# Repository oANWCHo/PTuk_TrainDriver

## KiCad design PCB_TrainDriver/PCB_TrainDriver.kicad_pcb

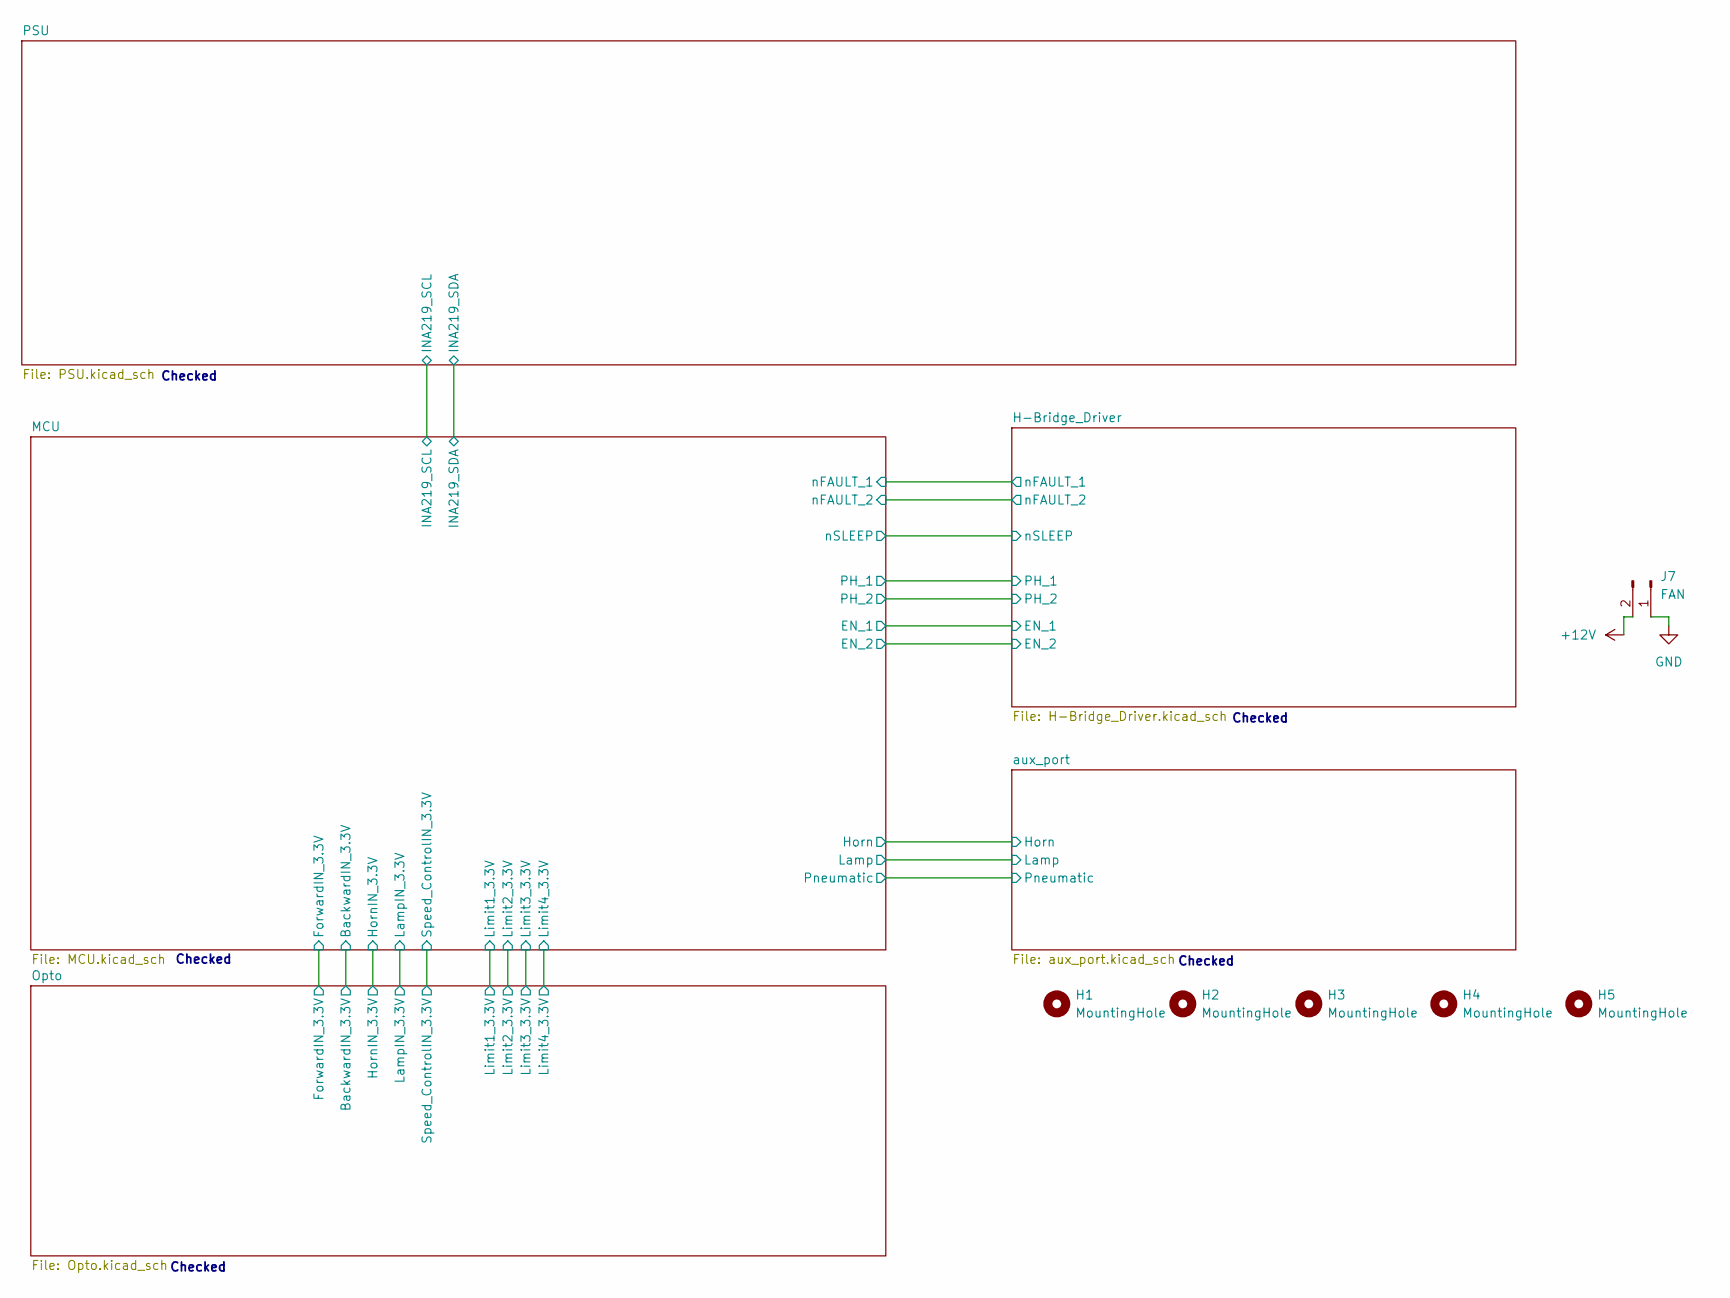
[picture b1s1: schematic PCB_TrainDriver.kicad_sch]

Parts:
H1, H2, H3, H4, H5: MountingHole; MountingHole_5.3mm_M5_DIN965_Pad
J7: FAN; JST_XA_B02B-XASK-1_1x02_P2.50mm_Vertical; JLCPCB Part # C265283

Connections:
+12V: J7.2; also elsewhere on the board
GND: J7.1; also elsewhere on the board

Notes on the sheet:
Checked

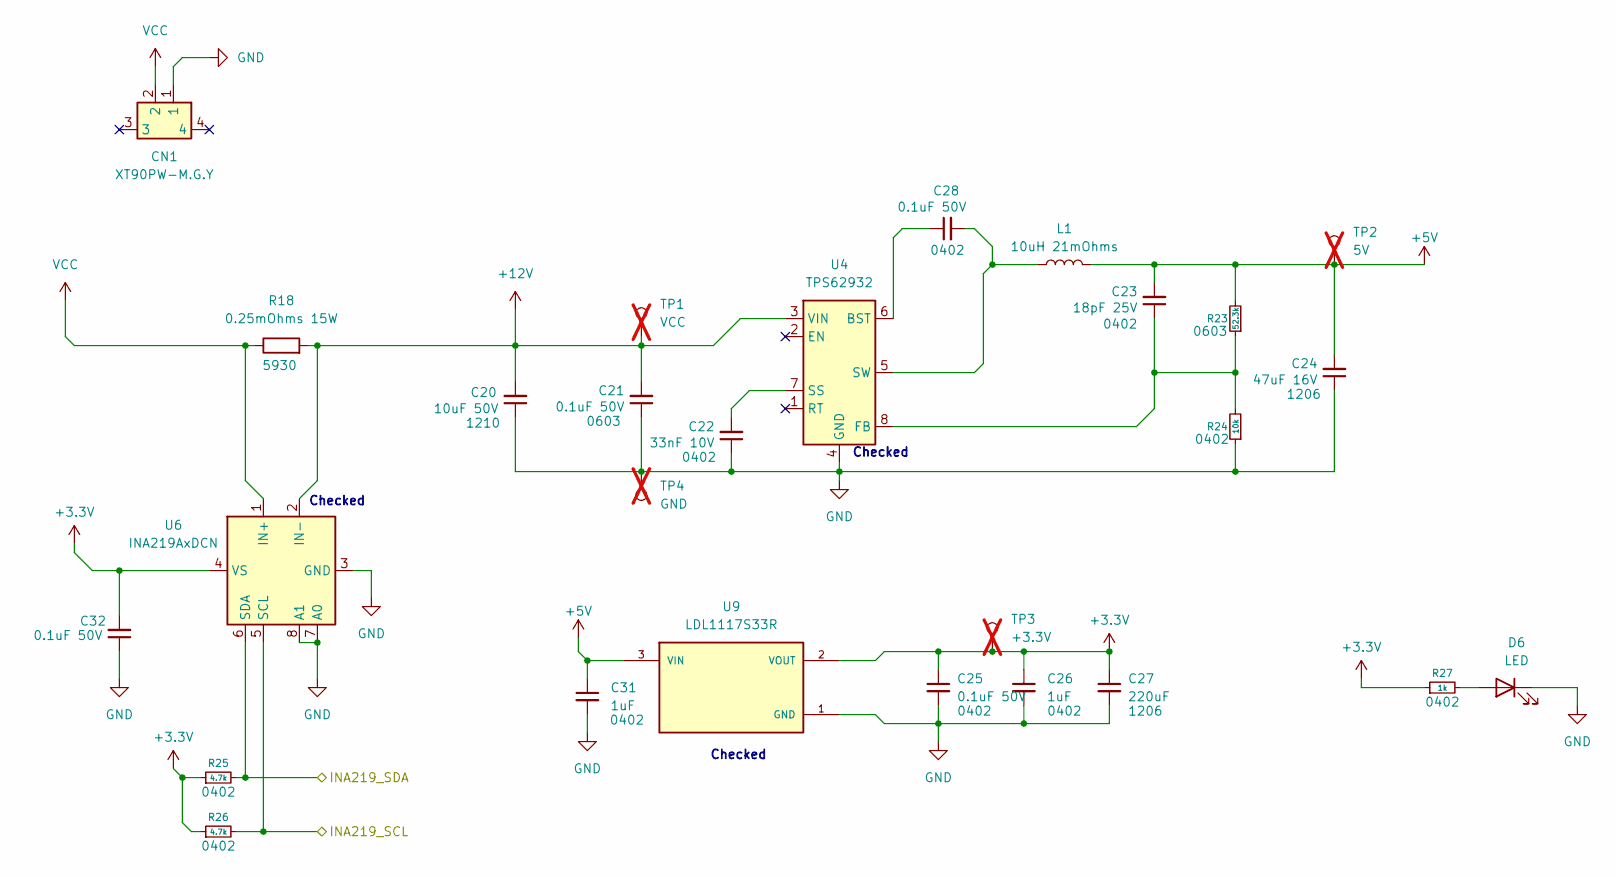
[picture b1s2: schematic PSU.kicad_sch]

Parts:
C20: 10uF 50V; C_1206_3216Metric; JLCPCB Part # C13585
C21: 0.1uF 50V; C_0603_1608Metric; JLCPCB Part # C14663
C22: 33nF 10V; C_0402_1005Metric; JLCPCB Part # C527022
C23: 18pF 25V; C_0402_1005Metric; JLCPCB Part # C526984
C24: 47uF 16V; C_1206_3216Metric; JLCPCB Part # C7472975
C25, C28, C32: 0.1uF 50V; C_0402_1005Metric; JLCPCB Part # C307331
C26, C31: 1uF; C_0402_1005Metric; JLCPCB Part # C52923
C27: 220uF; C_1206_3216Metric; JLCPCB Part # C412252
CN1: XT90PW-M.G.Y; CONN-TH_XT90PW-M.G.Y; Manufacturer Part XT90PW-M.G.Y; LCSC Part Name AMASS(艾迈斯)PCB焊板式卧式航模连接器 锂电池大电流插头 30A二芯P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
D6: LED; LED_0603_1608Metric; JLCPCB Part # C2286
L1: 10uH 21mOhms; L_12x12mm_H4.5mm; JLCPCB Part # C9904
R18: 0.25mOhms 15W; R5930; JLCPCB Part # C495779
R23: 52.3k; R_0603_1608Metric; JLCPCB Part # C23198
R24: 10k; R_0402_1005Metric; JLCPCB Part # C60490
R25, R26: 4.7k; R_0402_1005Metric; JLCPCB Part # C25900
R27: 1k; R_0402_1005Metric; JLCPCB Part # C11702
TP1: VCC; Pin_D0.7mm_L6.5mm_W1.8mm_FlatFork; not fitted
TP2: 5V; Pin_D0.7mm_L6.5mm_W1.8mm_FlatFork; not fitted
TP3: +3.3V; Pin_D0.7mm_L6.5mm_W1.8mm_FlatFork; not fitted
TP4: GND; Pin_D0.7mm_L6.5mm_W1.8mm_FlatFork; not fitted
U4: TPS62932; SOT-583-8; JLCPCB Part # C3032935
U6: INA219AxDCN; SOT-23-8; JLCPCB Part # C87469
U9: LDL1117S33R; SOT-223-3_TabPin2; PARTREV 7; JLCPCB Part # C18906017

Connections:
+3.3V: C25.1, C26.1, C27.1, C32.2, R25.1, R26.1, R27.1, TP3.1 (1_1), U6.4 (VS), U9.2 (VOUT), U9.4 (VOUT__1); also elsewhere on the board
+5V: C23.2, C24.2, C31.1, L1.2, R23.2, TP2.1 (1_1), U9.3 (VIN)
+12V: C20.2, C21.2, R18.2, TP1.1 (1_1), U4.3 (VIN), U6.2 (IN-); also elsewhere on the board
/MCU/INA219_SCL: R26.2, U6.5 (SCL); also elsewhere on the board
/MCU/INA219_SDA: R25.2, U6.6 (SDA); also elsewhere on the board
GND: C20.1, C21.1, C22.1, C24.1, C25.2, C26.2, C27.2, C31.2, C32.1, CN1.1, D6.1 (K), R24.1, TP4.1 (1_1), U4.4 (GND), U6.3 (GND), U6.7 (A0), U6.8 (A1), U9.1 (GND); also elsewhere on the board
unnamed: D6.2 (A), R27.2
unnamed: C28.1, U4.6 (BST)
unnamed: C23.1, R23.1, R24.2, U4.8 (FB)
unnamed: C22.2, U4.7 (SS)
unnamed: C28.2, L1.1, U4.5 (SW)
VCC: CN1.2, R18.1, U6.1 (IN+)

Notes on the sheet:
Checked

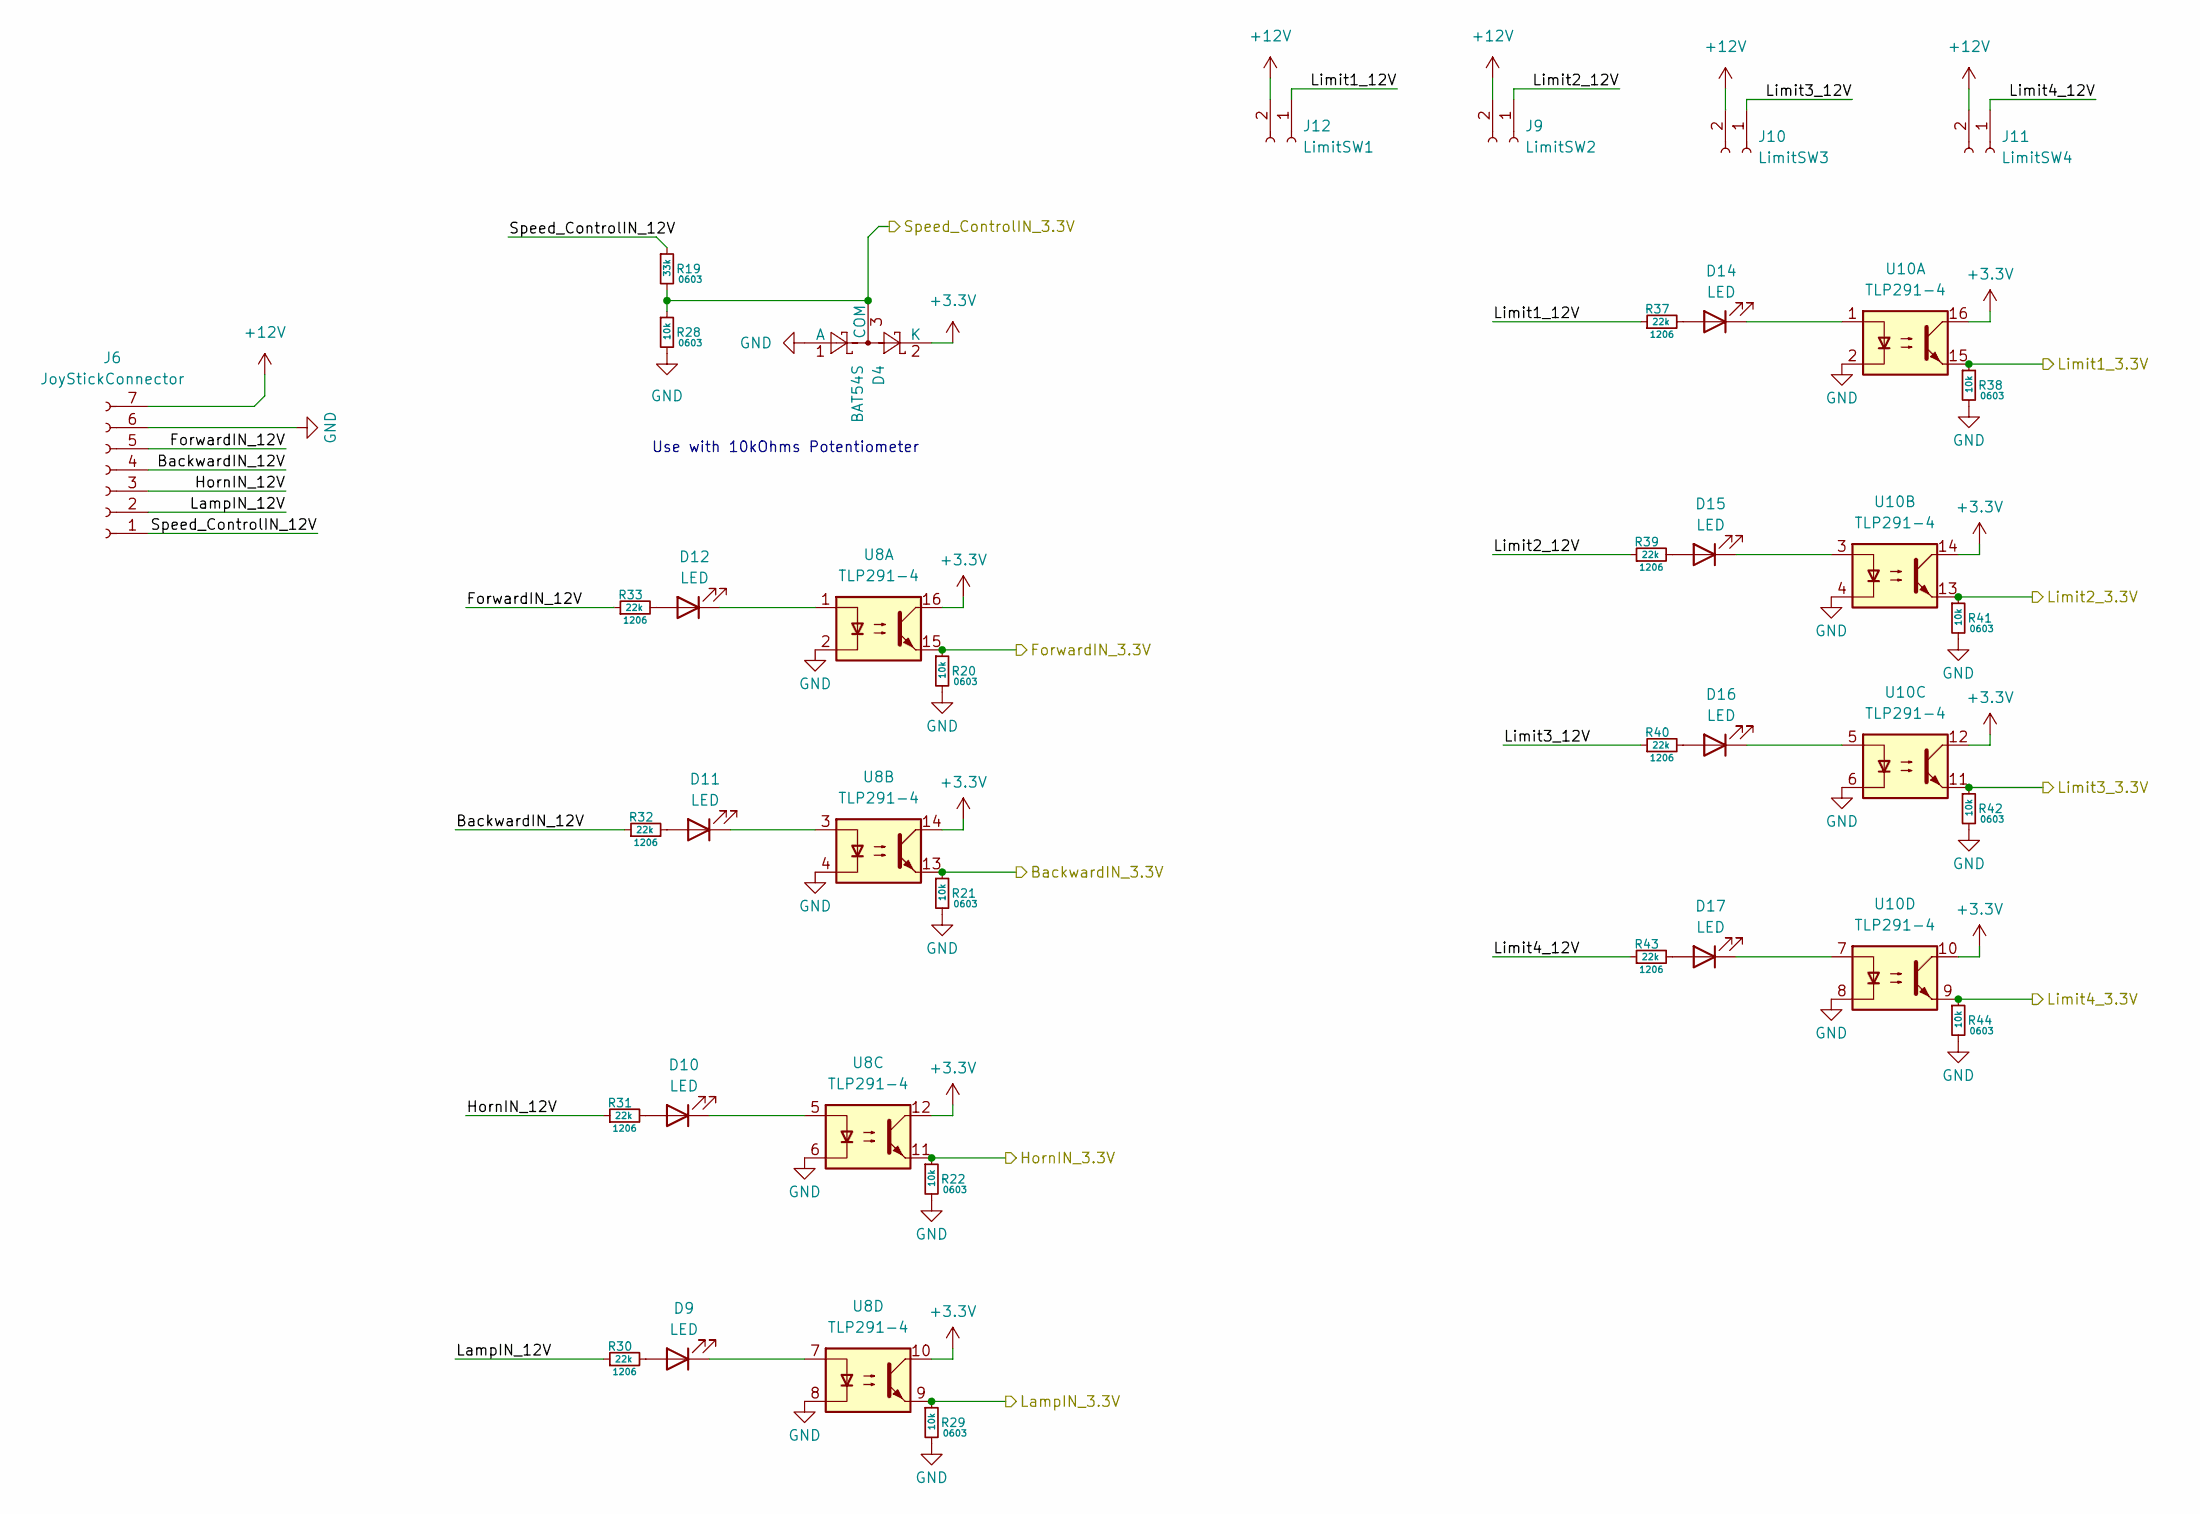
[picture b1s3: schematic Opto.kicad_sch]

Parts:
D4: BAT54S; SOT-23; JLCPCB Part # C19726
D9, D10, D11, D12, D14, D15, D16, D17: LED; LED_0603_1608Metric; JLCPCB Part # C2287
J6: JoyStickConnector; JST_XH_B7B-XH-A_1x07_P2.50mm_Vertical; JLCPCB Part # C144398
J9: LimitSW2; JST_XH_B2B-XH-A_1x02_P2.50mm_Vertical; JLCPCB Part # C265283
J10: LimitSW3; JST_XH_B2B-XH-A_1x02_P2.50mm_Vertical; JLCPCB Part # C265283
J11: LimitSW4; JST_XH_B2B-XH-A_1x02_P2.50mm_Vertical; JLCPCB Part # C265283
J12: LimitSW1; JST_XH_B2B-XH-A_1x02_P2.50mm_Vertical; JLCPCB Part # C265283
R19: 33k; R_0603_1608Metric; JLCPCB Part # C4216
R20, R21, R22, R28, R29, R38, R41, R42, R44: 10k; R_0603_1608Metric; JLCPCB Part # C25804
R30, R31, R32, R33, R37, R39, R40, R43: 22k; R_1206_3216Metric; JLCPCB Part # C25654
U8, U10: TLP291-4; SOIC-16_4.55x10.3mm_P1.27mm; JLCPCB Part # C60900

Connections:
+3.3V: D4.2 (K), U8.10, U8.12, U8.14, U8.16, U10.10, U10.12, U10.14, U10.16; also elsewhere on the board
+12V: J6.7, J9.2, J10.2, J11.2, J12.2; also elsewhere on the board
/MCU/BackwardIN_3.3V: R21.1, U8.13; also elsewhere on the board
/MCU/ForwardIN_3.3V: R20.1, U8.15; also elsewhere on the board
/MCU/HornIN_3.3V: R22.1, U8.11; also elsewhere on the board
/MCU/LampIN_3.3V: R29.1, U8.9; also elsewhere on the board
/MCU/Limit1_3.3V: R38.1, U10.15; also elsewhere on the board
/MCU/Limit2_3.3V: R41.1, U10.13; also elsewhere on the board
/MCU/Limit3_3.3V: R42.1, U10.11; also elsewhere on the board
/MCU/Limit4_3.3V: R44.1, U10.9; also elsewhere on the board
/MCU/Speed_ControlIN_3.3V: D4.3 (COM), R19.2, R28.1; also elsewhere on the board
/Opto/BackwardIN_12V: J6.4, R32.1
/Opto/ForwardIN_12V: J6.5, R33.1
/Opto/HornIN_12V: J6.3, R31.1
/Opto/LampIN_12V: J6.2, R30.1
/Opto/Limit1_12V: J12.1, R37.1
/Opto/Limit2_12V: J9.1, R39.1
/Opto/Limit3_12V: J10.1, R40.1
/Opto/Limit4_12V: J11.1, R43.1
/Opto/Speed_ControlIN_12V: J6.1, R19.1
GND: D4.1 (A), J6.6, R20.2, R21.2, R22.2, R28.2, R29.2, R38.2, R41.2, R42.2, R44.2, U8.2, U8.4, U8.6, U8.8, U10.2, U10.4, U10.6, U10.8; also elsewhere on the board
unnamed: D9.2 (A), R30.2
unnamed: D9.1 (K), U8.7
unnamed: D10.2 (A), R31.2
unnamed: D10.1 (K), U8.5
unnamed: D11.2 (A), R32.2
unnamed: D11.1 (K), U8.3
unnamed: D12.2 (A), R33.2
unnamed: D12.1 (K), U8.1
unnamed: D14.2 (A), R37.2
unnamed: D14.1 (K), U10.1
unnamed: D15.2 (A), R39.2
unnamed: D15.1 (K), U10.3
unnamed: D16.2 (A), R40.2
unnamed: D16.1 (K), U10.5
unnamed: D17.2 (A), R43.2
unnamed: D17.1 (K), U10.7

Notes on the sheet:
Use with 10kOhms Potentiometer

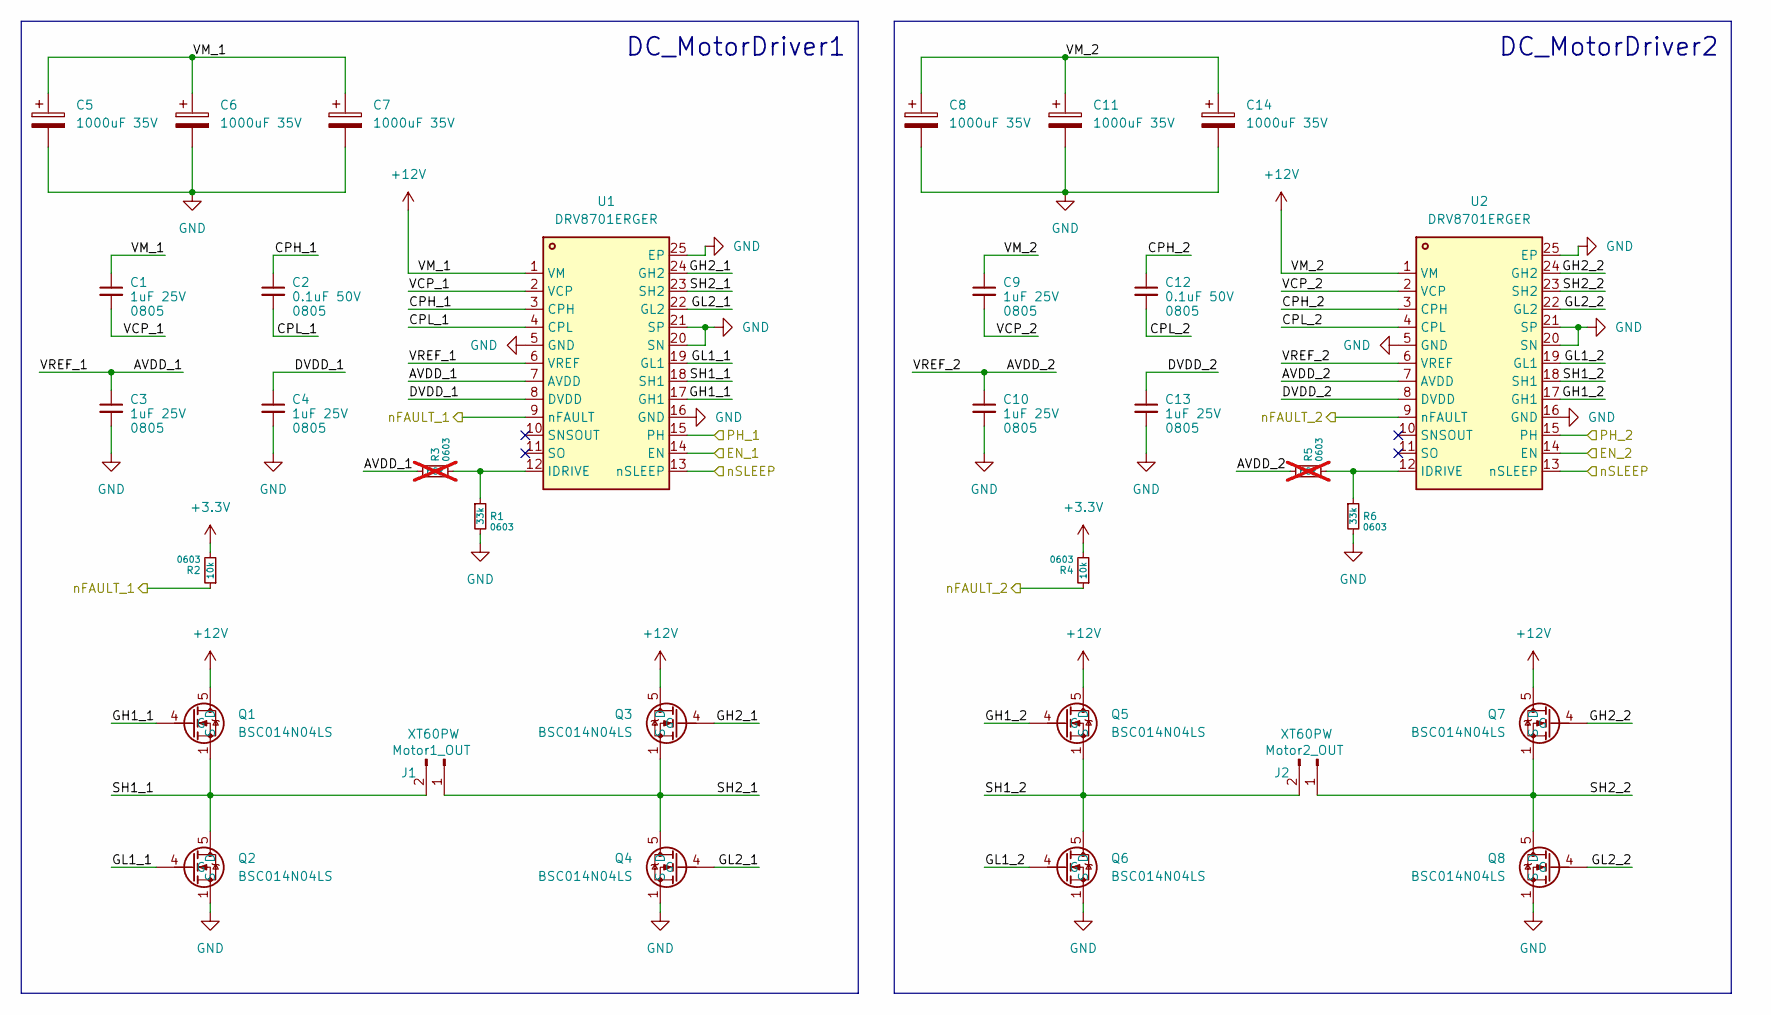
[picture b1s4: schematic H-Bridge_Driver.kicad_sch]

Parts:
C1, C3, C4, C9, C10, C13: 1uF 25V; C_0805_2012Metric; JLCPCB Part # C5137482
C2, C12: 0.1uF 50V; C_0805_2012Metric; JLCPCB Part # C49678
C5, C6, C7, C8, C11, C14: 1000uF 35V; CP_Elec_10x10; JLCPCB Part # C46550395
J1: Motor1_OUT; AMASS_XT60PW-M_1x02_P7.20mm_Horizontal; JLCPCB Part # C98732
J2: Motor2_OUT; AMASS_XT60PW-M_1x02_P7.20mm_Horizontal; JLCPCB Part # C98732
Q1, Q2, Q3, Q4, Q5, Q6, Q7, Q8: BSC014N04LS; Infineon_PG-TDSON-8_6.15x5.15mm; JLCPCB Part # C2760081
R1, R6: 33k; R_0603_1608Metric; JLCPCB Part # C4216
R2, R4: 10k; R_0603_1608Metric; JLCPCB Part # C25804
R3, R5: 68k; R_0603_1608Metric; JLCPCB Part # C23231; not fitted
U1, U2: DRV8701ERGER; VQFN-24-1EP_4x4mm_P0.5mm_EP2.45x2.45mm; Manufacturer Part DRV8701ERGER; JLCPCB Part # C90964

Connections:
+3.3V: R2.2, R4.2; also elsewhere on the board
+12V: C1.1, C5.1, C6.1, C7.1, C8.1, C9.1, C11.1, C14.1, Q1.5 (D), Q3.5 (D), Q5.5 (D), Q7.5 (D), U1.1 (VM), U2.1 (VM); also elsewhere on the board
/H-Bridge_Driver/AVDD_1: C3.1, R3.1, U1.6 (VREF), U1.7 (AVDD)
/H-Bridge_Driver/AVDD_2: C10.1, R5.1, U2.6 (VREF), U2.7 (AVDD)
/H-Bridge_Driver/CPH_1: C2.1, U1.3 (CPH)
/H-Bridge_Driver/CPH_2: C12.1, U2.3 (CPH)
/H-Bridge_Driver/CPL_1: C2.2, U1.4 (CPL)
/H-Bridge_Driver/CPL_2: C12.2, U2.4 (CPL)
/H-Bridge_Driver/DVDD_1: C4.1, U1.8 (DVDD)
/H-Bridge_Driver/DVDD_2: C13.1, U2.8 (DVDD)
/H-Bridge_Driver/EN_1: U1.14 (EN); also elsewhere on the board
/H-Bridge_Driver/EN_2: U2.14 (EN); also elsewhere on the board
/H-Bridge_Driver/GH1_1: Q1.4 (G), U1.17 (GH1)
/H-Bridge_Driver/GH1_2: Q5.4 (G), U2.17 (GH1)
/H-Bridge_Driver/GH2_1: Q3.4 (G), U1.24 (GH2)
/H-Bridge_Driver/GH2_2: Q7.4 (G), U2.24 (GH2)
/H-Bridge_Driver/GL1_1: Q2.4 (G), U1.19 (GL1)
/H-Bridge_Driver/GL1_2: Q6.4 (G), U2.19 (GL1)
/H-Bridge_Driver/GL2_1: Q4.4 (G), U1.22 (GL2)
/H-Bridge_Driver/GL2_2: Q8.4 (G), U2.22 (GL2)
/H-Bridge_Driver/PH_1: U1.15 (PH); also elsewhere on the board
/H-Bridge_Driver/PH_2: U2.15 (PH); also elsewhere on the board
/H-Bridge_Driver/SH1_1: J1.2, Q1.1 (S), Q1.2 (S), Q1.3 (S), Q2.5 (D), U1.18 (SH1)
/H-Bridge_Driver/SH1_2: J2.2, Q5.1 (S), Q5.2 (S), Q5.3 (S), Q6.5 (D), U2.18 (SH1)
/H-Bridge_Driver/SH2_1: J1.1, Q3.1 (S), Q3.2 (S), Q3.3 (S), Q4.5 (D), U1.23 (SH2)
/H-Bridge_Driver/SH2_2: J2.1, Q7.1 (S), Q7.2 (S), Q7.3 (S), Q8.5 (D), U2.23 (SH2)
/H-Bridge_Driver/VCP_1: C1.2, U1.2 (VCP)
/H-Bridge_Driver/VCP_2: C9.2, U2.2 (VCP)
/H-Bridge_Driver/nFAULT_1: R2.1, U1.9 (nFAULT); also elsewhere on the board
/H-Bridge_Driver/nFAULT_2: R4.1, U2.9 (nFAULT); also elsewhere on the board
/H-Bridge_Driver/nSLEEP: U1.13 (nSLEEP), U2.13 (nSLEEP); also elsewhere on the board
GND: C3.2, C4.2, C5.2, C6.2, C7.2, C8.2, C10.2, C11.2, C13.2, C14.2, Q2.1 (S), Q2.2 (S), Q2.3 (S), Q4.1 (S), Q4.2 (S), Q4.3 (S), Q6.1 (S), Q6.2 (S), Q6.3 (S), Q8.1 (S), Q8.2 (S), Q8.3 (S), R1.2, R6.2, U1.5 (GND), U1.16 (GND), U1.20 (SN), U1.21 (SP), U1.25 (EP), U2.5 (GND), U2.16 (GND), U2.20 (SN), U2.21 (SP), U2.25 (EP); also elsewhere on the board
unnamed: R1.1, R3.2, U1.12 (IDRIVE)
unnamed: R5.2, R6.1, U2.12 (IDRIVE)

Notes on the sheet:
DC_MotorDriver1
DC_MotorDriver2

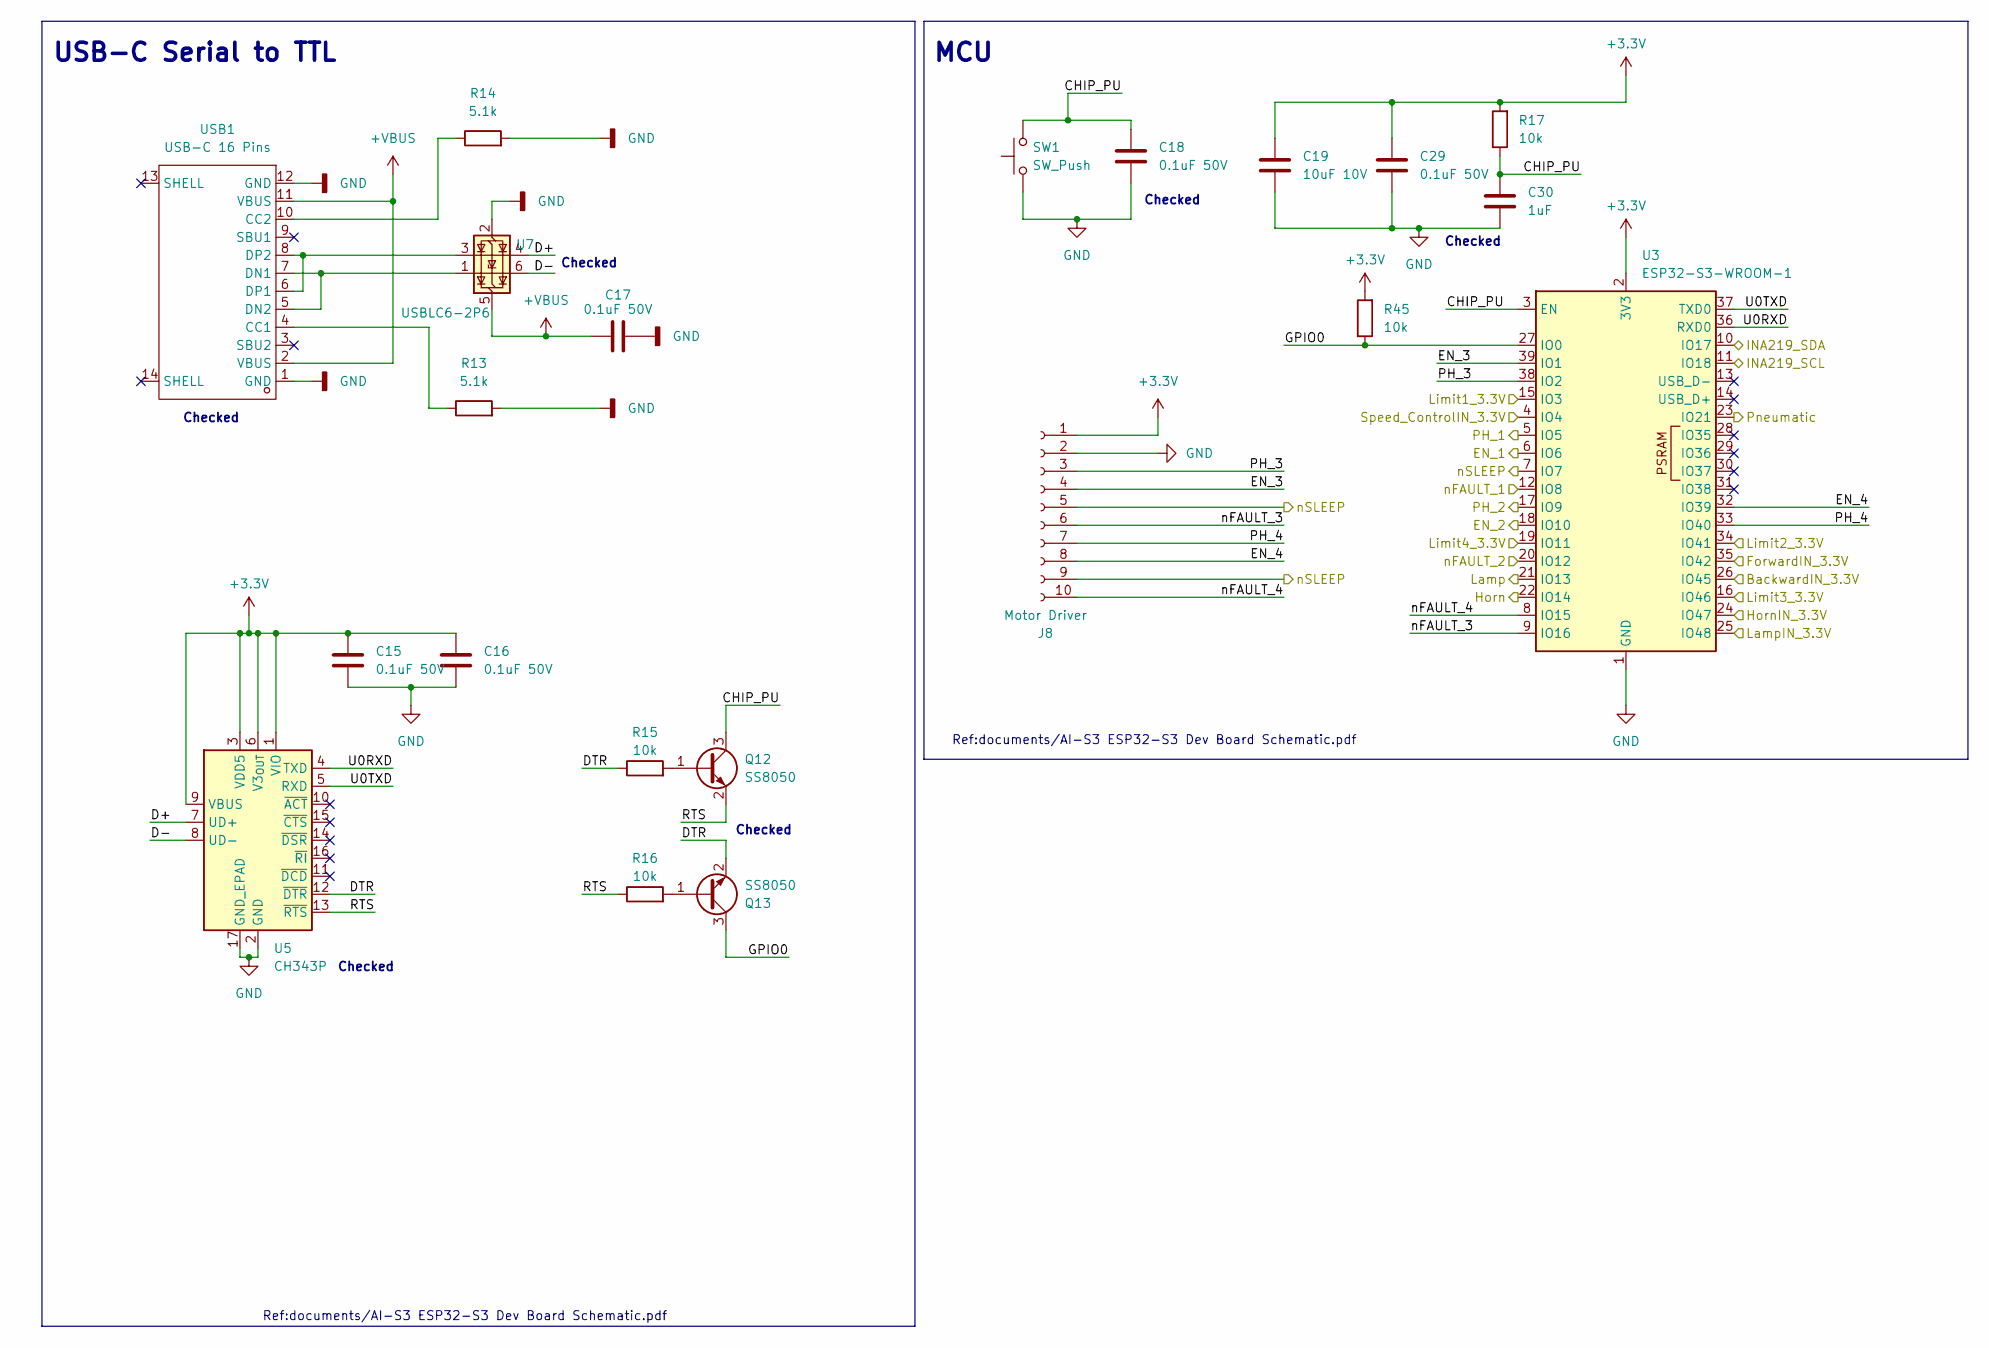
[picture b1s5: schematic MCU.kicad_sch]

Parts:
C15, C16, C17, C18, C29: 0.1uF 50V; C_0402_1005Metric; JLCPCB Part # C307331
C19: 10uF 10V; C_0402_1005Metric; JLCPCB Part # C2846677
C30: 1uF; C_0402_1005Metric; JLCPCB Part # C52923
J8: Motor Driver; JST_XH_B10B-XH-A_1x10_P2.50mm_Vertical; JLCPCB Part # C144400
Q12, Q13: SS8050; SOT-23; JLCPCB Part # C2150
R13, R14: 5.1k; R_0603_1608Metric; JLCPCB Part # C23186
R15, R16, R17, R45: 10k; R_0402_1005Metric; JLCPCB Part # C60490
SW1: SW_Push; SW_Tactile_SPST_NO_Straight_CK_PTS636Sx25SMTRLFS; JLCPCB Part # C118141
U3: ESP32-S3-WROOM-1; JLCPCB Part # C2913198
U5: CH343P; WCH_QFN-16-1EP_3x3mm_P0.5mm_EP1.8x1.8mm; JLCPCB Part # C2846043
U7: USBLC6-2P6; SOT-666; JLCPCB Part # C15999
USB1: USB-C 16 Pins; USB-C-SMD_TYPE-C-16PIN; Manufacturer Part TYPE-C 16PIN 2MD(073); JLCPCB Part # C393939

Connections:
+3.3V: C15.1, C16.1, C19.1, C29.1, J8.1, R17.2, R45.2, U3.2 (3V3), U5.1 (VIO), U5.3 (VDD5), U5.6 (V3_{OUT}), U5.9 (VBUS); also elsewhere on the board
+VBUS: C17.1, U7.5 (VBUS), USB1.2 (VBUS), USB1.11 (VBUS)
/H-Bridge_Driver/EN_1: U3.6 (IO6); also elsewhere on the board
/H-Bridge_Driver/EN_2: U3.18 (IO10); also elsewhere on the board
/H-Bridge_Driver/PH_1: U3.5 (IO5); also elsewhere on the board
/H-Bridge_Driver/PH_2: U3.17 (IO9); also elsewhere on the board
/H-Bridge_Driver/nFAULT_1: U3.12 (IO8); also elsewhere on the board
/H-Bridge_Driver/nFAULT_2: U3.20 (IO12); also elsewhere on the board
/H-Bridge_Driver/nSLEEP: J8.5, J8.9, U3.7 (IO7); also elsewhere on the board
/MCU/BackwardIN_3.3V: U3.26 (IO45); also elsewhere on the board
/MCU/CHIP_PU: C18.1, C30.1, Q12.3 (C), R17.1, SW1.2, U3.3 (EN)
/MCU/D+: U5.7 (UD+), U7.4 (I/O2)
/MCU/D-: U5.8 (UD-), U7.6 (I/O1)
/MCU/DTR: Q13.2 (E), R15.1, U5.12 (~DTR)
/MCU/EN_3: J8.4, U3.39 (IO1)
/MCU/EN_4: J8.8, U3.32 (IO39)
/MCU/ForwardIN_3.3V: U3.35 (IO42); also elsewhere on the board
/MCU/GPIO0: Q13.3 (C), R45.1, U3.27 (IO0)
/MCU/Horn: U3.22 (IO14); also elsewhere on the board
/MCU/HornIN_3.3V: U3.24 (IO47); also elsewhere on the board
/MCU/INA219_SCL: U3.11 (IO18); also elsewhere on the board
/MCU/INA219_SDA: U3.10 (IO17); also elsewhere on the board
/MCU/Lamp: U3.21 (IO13); also elsewhere on the board
/MCU/LampIN_3.3V: U3.25 (IO48); also elsewhere on the board
/MCU/Limit1_3.3V: U3.15 (IO3); also elsewhere on the board
/MCU/Limit2_3.3V: U3.34 (IO41); also elsewhere on the board
/MCU/Limit3_3.3V: U3.16 (IO46); also elsewhere on the board
/MCU/Limit4_3.3V: U3.19 (IO11); also elsewhere on the board
/MCU/PH_3: J8.3, U3.38 (IO2)
/MCU/PH_4: J8.7, U3.33 (IO40)
/MCU/Pneumatic: U3.23 (IO21); also elsewhere on the board
/MCU/RTS: Q12.2 (E), R16.1, U5.13 (~RTS)
/MCU/Speed_ControlIN_3.3V: U3.4 (IO4); also elsewhere on the board
/MCU/U0RXD: U3.36 (RXD0), U5.4 (TXD)
/MCU/U0TXD: U3.37 (TXD0), U5.5 (RXD)
/MCU/nFAULT_3: J8.6, U3.9 (IO16)
/MCU/nFAULT_4: J8.10, U3.8 (IO15)
GND: C15.2, C16.2, C17.2, C18.2, C19.2, C29.2, C30.2, J8.2, R13.2, R14.2, SW1.1, U3.1 (GND), U3.40 (GND), U3.41 (GND), U5.2 (GND), U5.17 (GND_EPAD), U7.2 (GND), USB1.1 (GND), USB1.12 (GND); also elsewhere on the board
unnamed: Q12.1 (B), R15.2
unnamed: Q13.1 (B), R16.2
unnamed: R13.1, USB1.4 (CC1)
unnamed: R14.1, USB1.10 (CC2)
unnamed: U7.1 (I/O1), USB1.5 (DN2), USB1.7 (DN1)
unnamed: U7.3 (I/O2), USB1.6 (DP1), USB1.8 (DP2)

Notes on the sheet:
Checked
Ref:documents/AI-S3 ESP32-S3 Dev Board Schematic.pdf
MCU
USB-C Serial to TTL

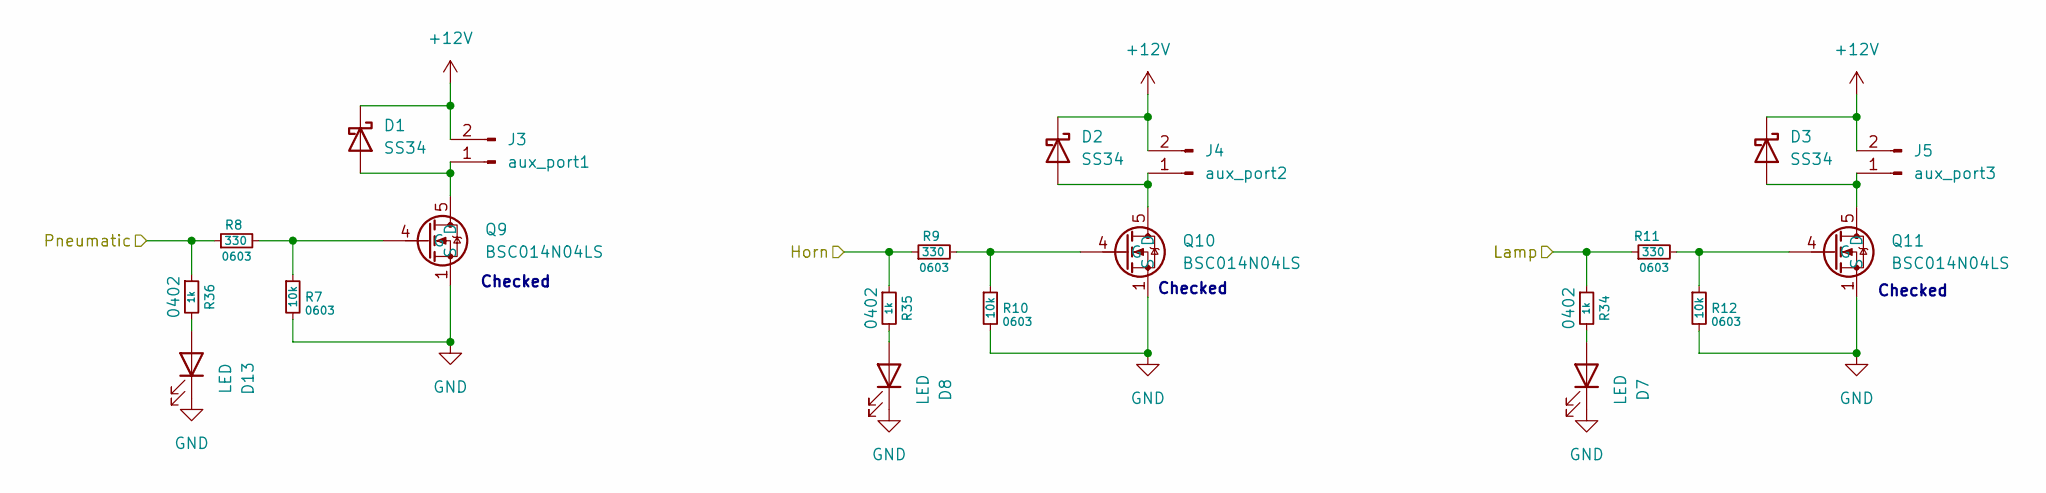
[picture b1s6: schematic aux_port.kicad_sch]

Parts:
D1, D2, D3: SS34; D_SMA; JLCPCB Part # C8678
D7, D8, D13: LED; LED_0603_1608Metric; JLCPCB Part # C2286
J3: aux_port1; AMASS_XT30PW-M_1x02_P2.50mm_Horizontal; JLCPCB Part # C431092
J4: aux_port2; AMASS_XT30PW-M_1x02_P2.50mm_Horizontal; JLCPCB Part # C431092
J5: aux_port3; AMASS_XT30PW-M_1x02_P2.50mm_Horizontal; JLCPCB Part # C431092
Q9, Q10, Q11: BSC014N04LS; Infineon_PG-TDSON-8_6.15x5.15mm; JLCPCB Part # C2760081
R7, R10, R12: 10k; R_0603_1608Metric; JLCPCB Part # C25804
R8, R9, R11: 330; R_0603_1608Metric; JLCPCB Part # C23138
R34, R35, R36: 1k; R_0402_1005Metric; JLCPCB Part # C11702

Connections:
+12V: D1.1 (K), D2.1 (K), D3.1 (K), J3.2, J4.2, J5.2; also elsewhere on the board
/MCU/Horn: R9.1, R35.1; also elsewhere on the board
/MCU/Lamp: R11.1, R34.1; also elsewhere on the board
/MCU/Pneumatic: R8.1, R36.1; also elsewhere on the board
GND: D7.1 (K), D8.1 (K), D13.1 (K), Q9.1 (S), Q9.2 (S), Q9.3 (S), Q10.1 (S), Q10.2 (S), Q10.3 (S), Q11.1 (S), Q11.2 (S), Q11.3 (S), R7.2, R10.2, R12.2; also elsewhere on the board
unnamed: D1.2 (A), J3.1, Q9.5 (D)
unnamed: D2.2 (A), J4.1, Q10.5 (D)
unnamed: D3.2 (A), J5.1, Q11.5 (D)
unnamed: D7.2 (A), R34.2
unnamed: D8.2 (A), R35.2
unnamed: D13.2 (A), R36.2
unnamed: Q9.4 (G), R7.1, R8.2
unnamed: Q10.4 (G), R9.2, R10.1
unnamed: Q11.4 (G), R11.2, R12.1

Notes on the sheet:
Checked

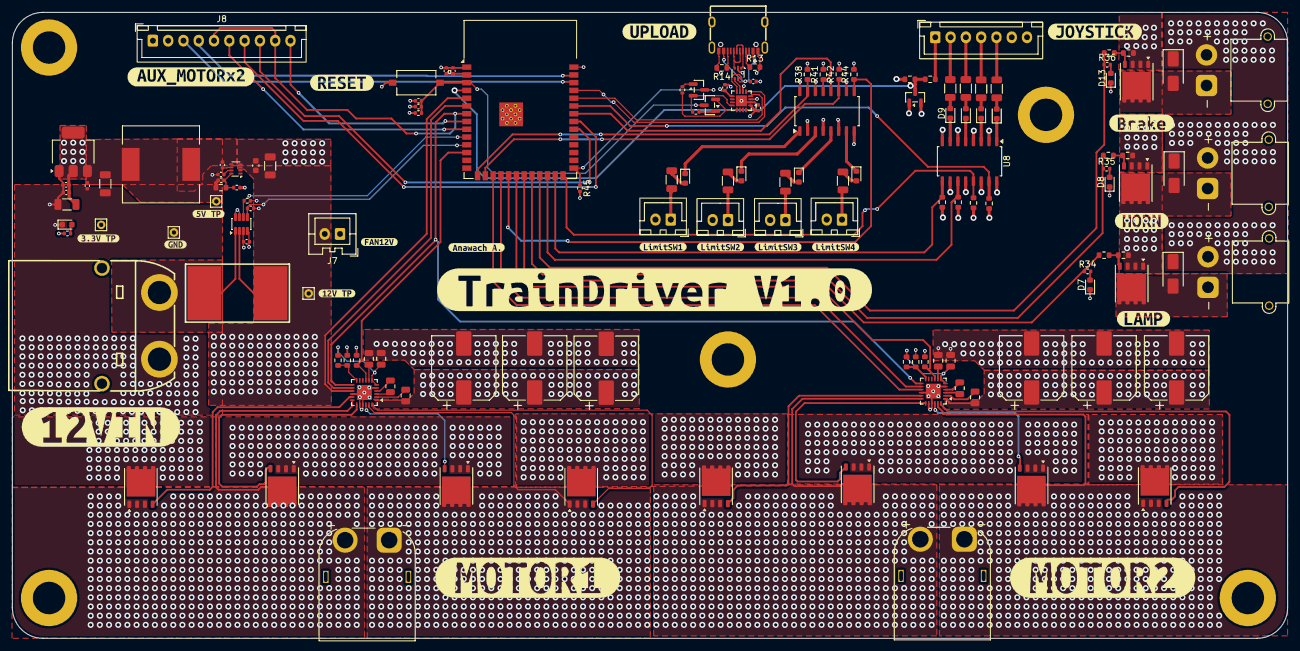
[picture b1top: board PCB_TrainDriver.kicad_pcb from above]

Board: 4 copper layers, 208.5 x 102.3 mm, 162 parts (0 on the bottom side), 110 nets.

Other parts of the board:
kibuzzard-6A50A23A: G***; kibuzzard-6A50A23A
kibuzzard-6A412E6E: G***; kibuzzard-6A412E6E
kibuzzard-6A412E9B: G***; kibuzzard-6A412E9B
kibuzzard-6A412E14: G***; kibuzzard-6A412E14
kibuzzard-6A412E20: G***; kibuzzard-6A412E20
kibuzzard-6A412E33: G***; kibuzzard-6A412E33
kibuzzard-6A412E56: G***; kibuzzard-6A412E56
kibuzzard-6A412EAB: G***; kibuzzard-6A412EAB
kibuzzard-6A412ECC: G***; kibuzzard-6A412ECC
kibuzzard-6A412EE2: G***; kibuzzard-6A412EE2
kibuzzard-6A412F0B: G***; kibuzzard-6A412F0B
kibuzzard-6A412F26: G***; kibuzzard-6A412F26
kibuzzard-6A412FC6: G***; kibuzzard-6A412FC6
kibuzzard-6A412FD5: G***; kibuzzard-6A412FD5
kibuzzard-6A412FE5: G***; kibuzzard-6A412FE5
kibuzzard-6A412FEF: G***; kibuzzard-6A412FEF
kibuzzard-6A536EEE: G***; kibuzzard-6A536EEE
kibuzzard-6A538FDD: G***; kibuzzard-6A538FDD
kibuzzard-6A538FF4: G***; kibuzzard-6A538FF4
kibuzzard-6A538FFC: G***; kibuzzard-6A538FFC
kibuzzard-6A539003: G***; kibuzzard-6A539003
